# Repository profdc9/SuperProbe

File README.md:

This is a KiCad implementation of Carlson's Superprobe by Daniel L. Marks, KW4TI.

It integrates the probe into the PCB by using the ground plane and vias to shield the probe.  The solder mask is left off of the area around the probe so that the probe can be taped over with copper or aluminum tape for extra shielding.

The PCB design is distributed under the Creative Commons Shared Alike Attribution (CC-BY-SA 4.0) license.

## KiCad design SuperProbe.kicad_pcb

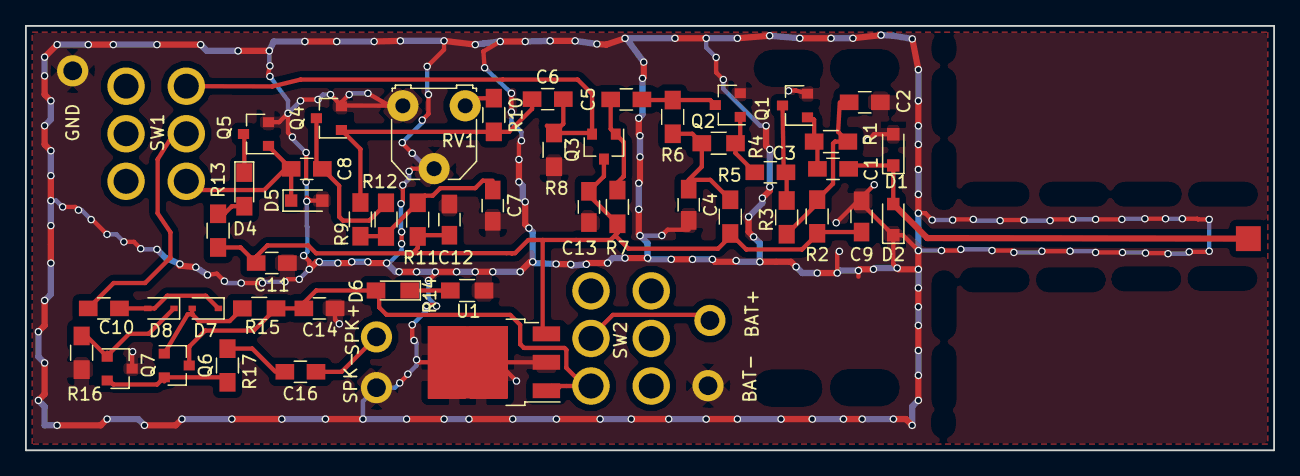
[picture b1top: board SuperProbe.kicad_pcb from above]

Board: 2 copper layers, 100.0 x 34.0 mm, 74 parts (0 on the bottom side), 28 nets.

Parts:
C1, C3: 10 nF; C_0805_HandSoldering
C2, C4, C7, C16: 22 uF; C_0805_HandSoldering
C5, C6, C10: 100 nF; C_0805_HandSoldering
C8: 330 pF; C_0805_HandSoldering
C9, C11, C12, C13, C14: 1 uF; C_0805_HandSoldering
D1, D2: 1N4148WS; D_SOD-323_HandSoldering
D4, D6: LED; LED_0805_HandSoldering
D5: LRB751V; D_SOD-323_HandSoldering
D7, D8: 1N4148WS; D_SOD-323
J1, J16, J17, J18, J19, J24: Conn_01x01; PadHole
J2, J3, J4, J5, J6, J7, J8, J9, J10, J11, J12, J13, J14, J15, J20, J21, J22, J23: Conn_01x01; BigSlot
Q1, Q2, Q3, Q4, Q5: MMBT3904; SOT-23
Q6: SS8050; SOT-23
Q7: SS8550; SOT-23
R1, R4, R7, R9: 2M2; R_0805_HandSoldering
R2, R5, R11, R13, R14: 1k; R_0805_HandSoldering
R3, R6, R12: 15k; R_0805_HandSoldering
R8: 2k7; R_0805_HandSoldering
R10: 330k; R_0805_HandSoldering
R15, R16: 10k; R_0805_HandSoldering
R17: 47R; R_0805_HandSoldering
RV1: 100k; Potentiometer_Triwood_RM-065
SW1: SW_SPDT; DPDTsmallswitch
SW2: SW_DPDT_x2; DPDTsmallswitch
U1: LM78M05_TO252; TO-252-3_TabPin2

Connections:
+5V: C9.2, C11.2, C12.2, C13.2, Q3.3, R2.1, R5.1, R7.1, R11.1, R13.1, U1.3
+9V: C14.2, D6.2, Q6.3, R15.1, SW2.4, U1.1
GND: C2.2, C4.2, C7.2, C9.1, C11.1, C12.1, C13.1, C14.1, D1.2, D2.1, D5.2, J16.1, J19.1, J24.1, Q1.2, Q2.2, Q4.2, Q5.2, Q7.3, R8.2, R14.2, R16.2, RV1.2, RV1.3, U1.2
unnamed: C1.1, Q1.1, R1.2
unnamed: C1.2, D1.1, D2.2, J1.1
unnamed: C2.1, R1.1, R2.2, R3.1
unnamed: C3.1, Q2.1, R4.2
unnamed: C3.2, Q1.3, R3.2
unnamed: C4.1, R4.1, R5.2, R6.1
unnamed: C5.1, Q3.1, R7.2
unnamed: C5.2, Q2.3, R6.2
unnamed: C6.1, Q4.1, R9.2, R10.1
unnamed: C6.2, Q3.2, R8.1, SW1.3
unnamed: C7.1, R9.1, R11.2, R12.1
unnamed: C8.1, D5.1, Q5.1, SW1.1
unnamed: C8.2, Q4.3, R12.2
unnamed: C10.1, D7.1, D8.2
unnamed: C10.2, SW1.2
unnamed: C16.1, J17.1
unnamed: C16.2, R17.1
unnamed: D4.1, Q5.3
unnamed: D4.2, R13.2
unnamed: D6.1, R14.1
unnamed: D7.2, Q6.1, R15.2
unnamed: D8.1, Q7.1, R16.1
unnamed: J18.1, SW2.5
unnamed: Q6.2, Q7.2, R17.2
unnamed: R10.2, RV1.1

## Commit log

2020-04-19 Committed all files
2020-04-19 Removed solder mask from ring around the board
2020-04-19 Added pcb kicad
2020-04-19 Before getting rid of the coin cells
2020-04-19 Uses 9 volt battery and board shrink
2020-04-23 Cleaned up the board slightly
2020-04-23 Added PadHole.kicad_mod
2020-05-07 Eliminated unneeded diode
